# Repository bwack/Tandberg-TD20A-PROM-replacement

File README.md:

# Tandberg-TD20A-PROM-replacement

A few attempts to solve the problematic, hard to get, hard to program PROM in the Tandberg TD20A Reel to Reel Tape Recorder PROM (U3).

Assembler program written by BWACK 2020.
ROM dumps by Knut Baardsen. RIP. You will always be missed.

Cut pin15 for 15 IPS, ground pin15 for 7.5 IPS

This project was successful. A chip is now installed in a real product that needed repair.
You can see all about it in these two videos:

## Programming

I used the TL866. Load the hex file, set the correct fuses (see the .fuses file).
For myself I have installed minipro on ubuntu, and this is what I run:

minipro -p ATTINY2313 -c code -f ihex -w tda20_prom_attiny2313.hex && \
minipro -p ATTINY2313 -c config -w tda20_prom_attiny2313.fuses

## YouTube videos:

TD20 update video showing the chip in action:

")

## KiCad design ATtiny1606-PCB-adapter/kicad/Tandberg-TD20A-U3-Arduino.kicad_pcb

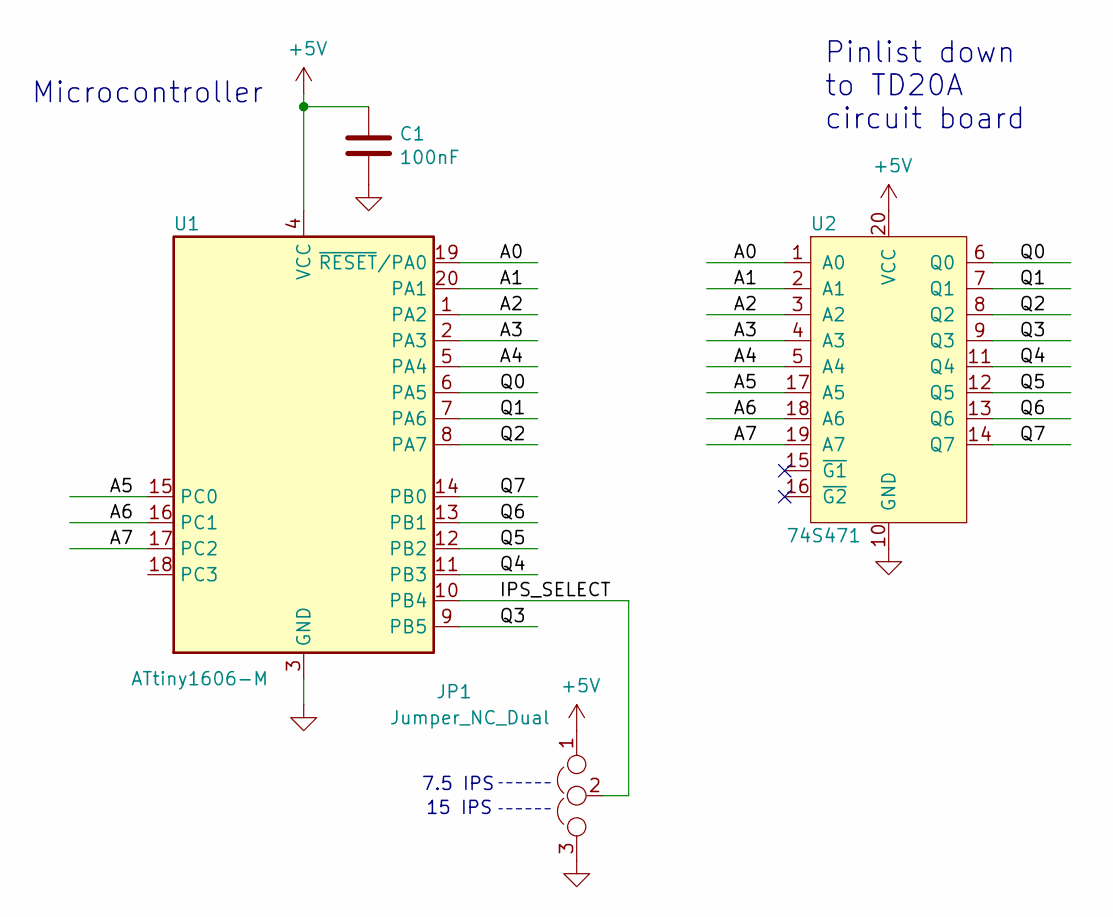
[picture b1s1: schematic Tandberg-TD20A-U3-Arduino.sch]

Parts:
C1: 100nF; C_0603_1608Metric_Pad1.05x0.95mm_HandSolder
JP1: Jumper_NC_Dual; SolderJumper-3_P1.3mm_Open_RoundedPad1.0x1.5mm_NumberLabels
U1: ATtiny1606-M; VQFN-20-1EP_3x3mm_P0.4mm_EP1.7x1.7mm
U2: 74S471; DIP-20_W7.62mm

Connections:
+5V: C1.1, JP1.1, U1.4 (VCC), U2.20 (VCC)
/A0: U1.19 (~RESET~/PA0), U2.1 (A0)
/A1: U1.20 (PA1), U2.2 (A1)
/A2: U1.1 (PA2), U2.3 (A2)
/A3: U1.2 (PA3), U2.4 (A3)
/A4: U1.5 (PA4), U2.5 (A4)
/A5: U1.15 (PC0), U2.17 (A5)
/A6: U1.16 (PC1), U2.18 (A6)
/A7: U1.17 (PC2), U2.19 (A7)
/IPS_SELECT: JP1.2, U1.10 (PB4)
/Q0: U1.6 (PA5), U2.6 (Q0)
/Q1: U1.7 (PA6), U2.7 (Q1)
/Q2: U1.8 (PA7), U2.8 (Q2)
/Q3: U1.9 (PB5), U2.9 (Q3)
/Q4: U1.11 (PB3), U2.11 (Q4)
/Q5: U1.12 (PB2), U2.12 (Q5)
/Q6: U1.13 (PB1), U2.13 (Q6)
/Q7: U1.14 (PB0), U2.14 (Q7)
GND: C1.2, JP1.3, U1.3 (GND), U1.21 (GND), U2.10 (GND)

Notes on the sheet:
7.5 IPS
15 IPS
Microcontroller
Pinlist down to TD20A circuit board

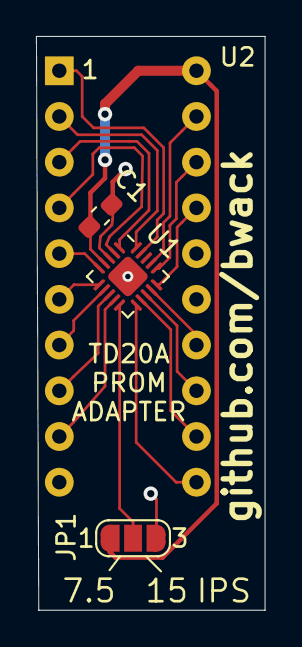
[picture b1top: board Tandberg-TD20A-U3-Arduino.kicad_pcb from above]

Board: 2 copper layers, 12.7 x 31.9 mm, 4 parts (0 on the bottom side), 19 nets.

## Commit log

2020-10-24 maintain pullups
2020-10-26 Fixed a major bug. Double pipe in ()|() statement.
2020-11-02 removed the adapter from this project. changed readme
2020-11-03 added ATtiny2313A
2020-11-05 update readme. added fuse-file for ATTINY2313A
